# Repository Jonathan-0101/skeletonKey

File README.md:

# Skeleton Key

Final year BEng Project, creating a Penetration Testing Device based on an ESP32 microcontroller, to highlight common and prevelent security vulnerabilities in devices and networks.

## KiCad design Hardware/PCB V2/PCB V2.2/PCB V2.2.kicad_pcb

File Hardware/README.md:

# Project Hardware

The schematics and PCB designs for the device are contained in this directory, designed in KiCad.

It would not have been possible to create the project without the assistance of open source designs and resources, most notibly from [Adafruit Industries](https://github.com/adafruit) and [Flipper Devices](https://github.com/flipperdevices)

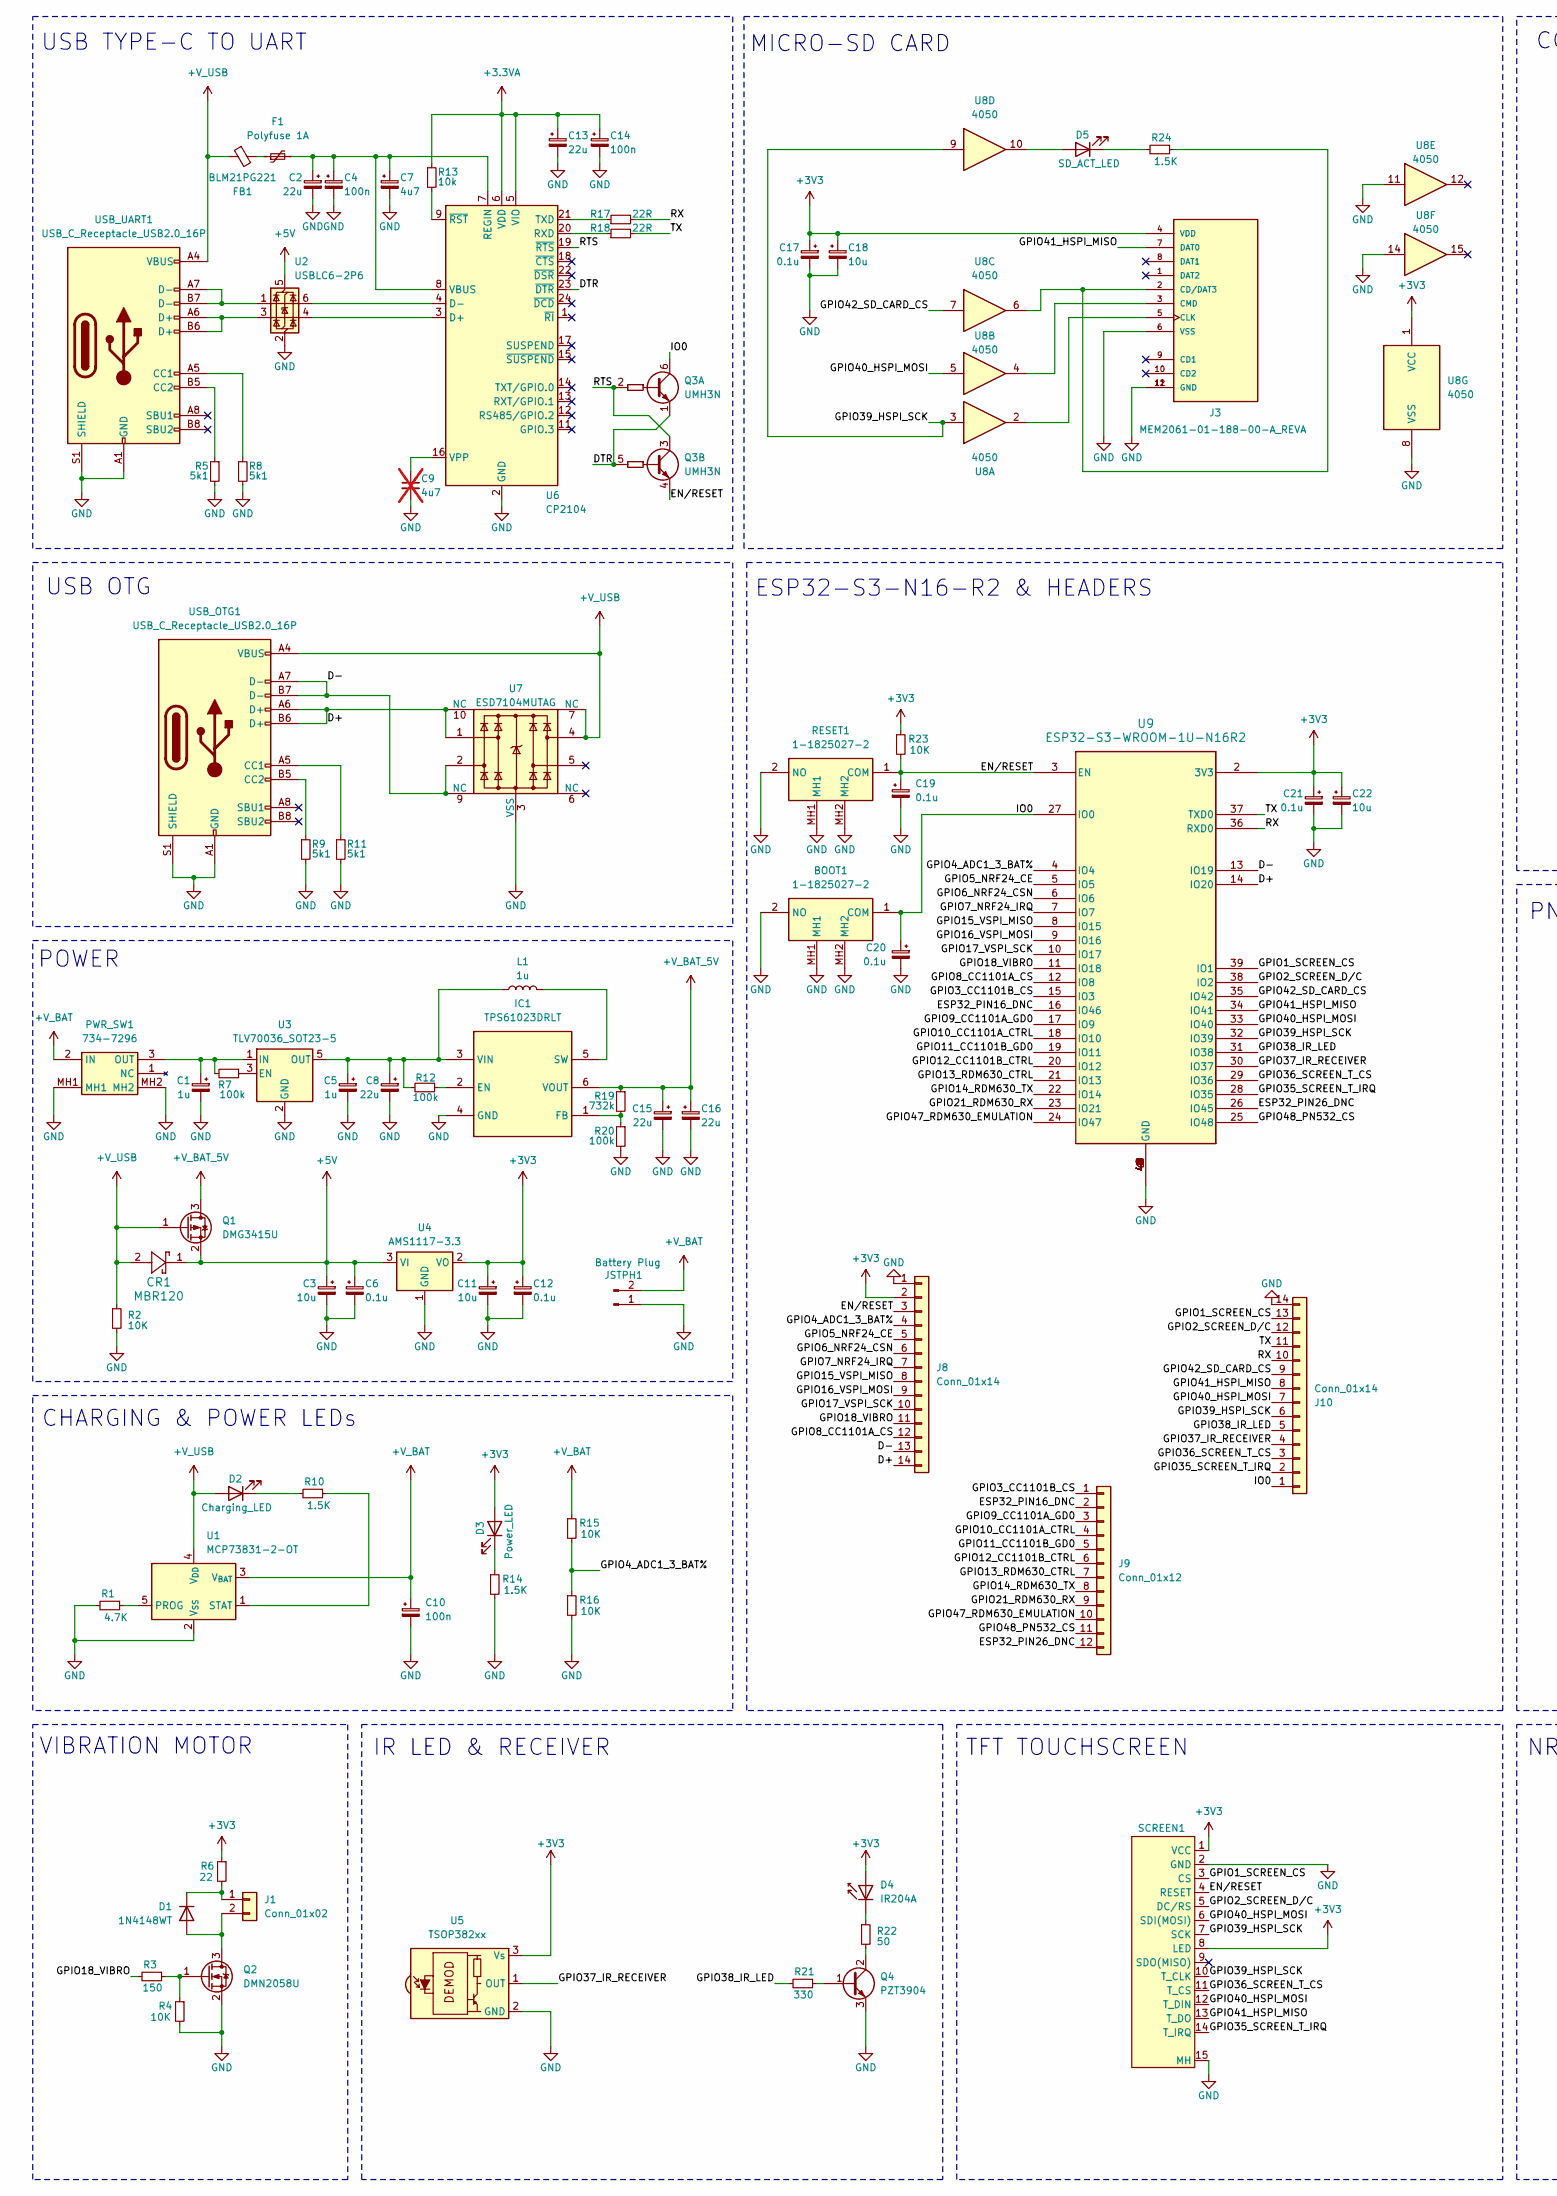
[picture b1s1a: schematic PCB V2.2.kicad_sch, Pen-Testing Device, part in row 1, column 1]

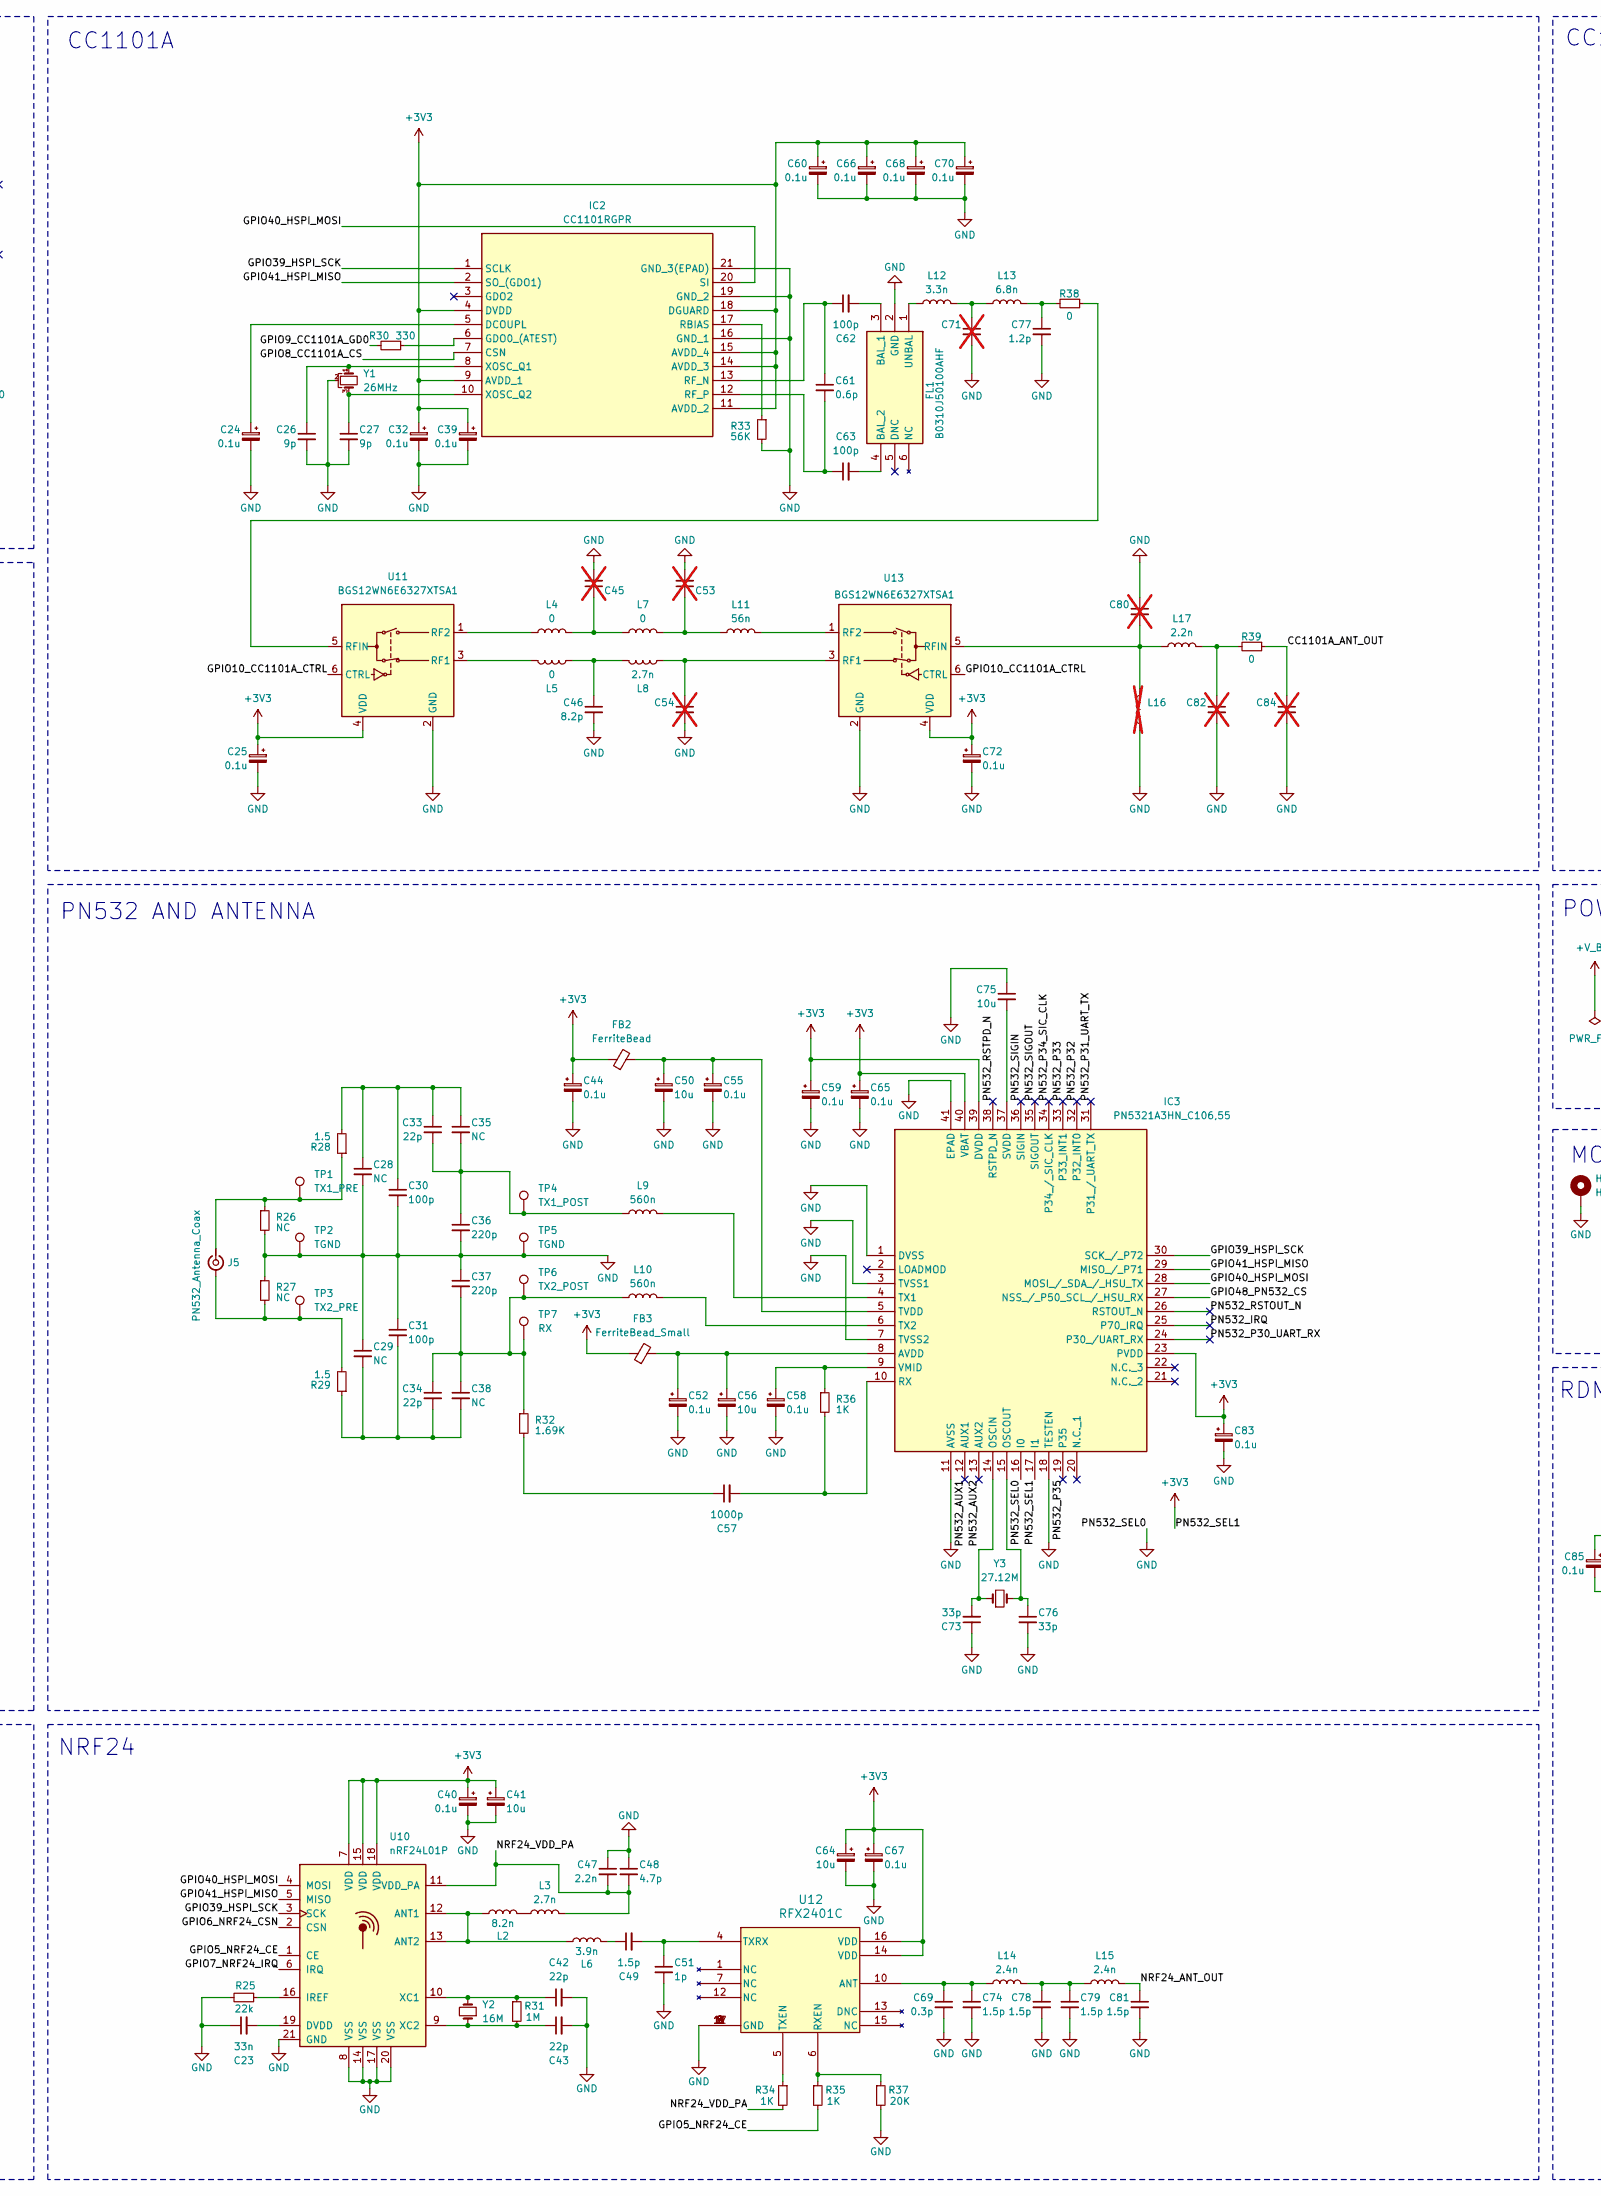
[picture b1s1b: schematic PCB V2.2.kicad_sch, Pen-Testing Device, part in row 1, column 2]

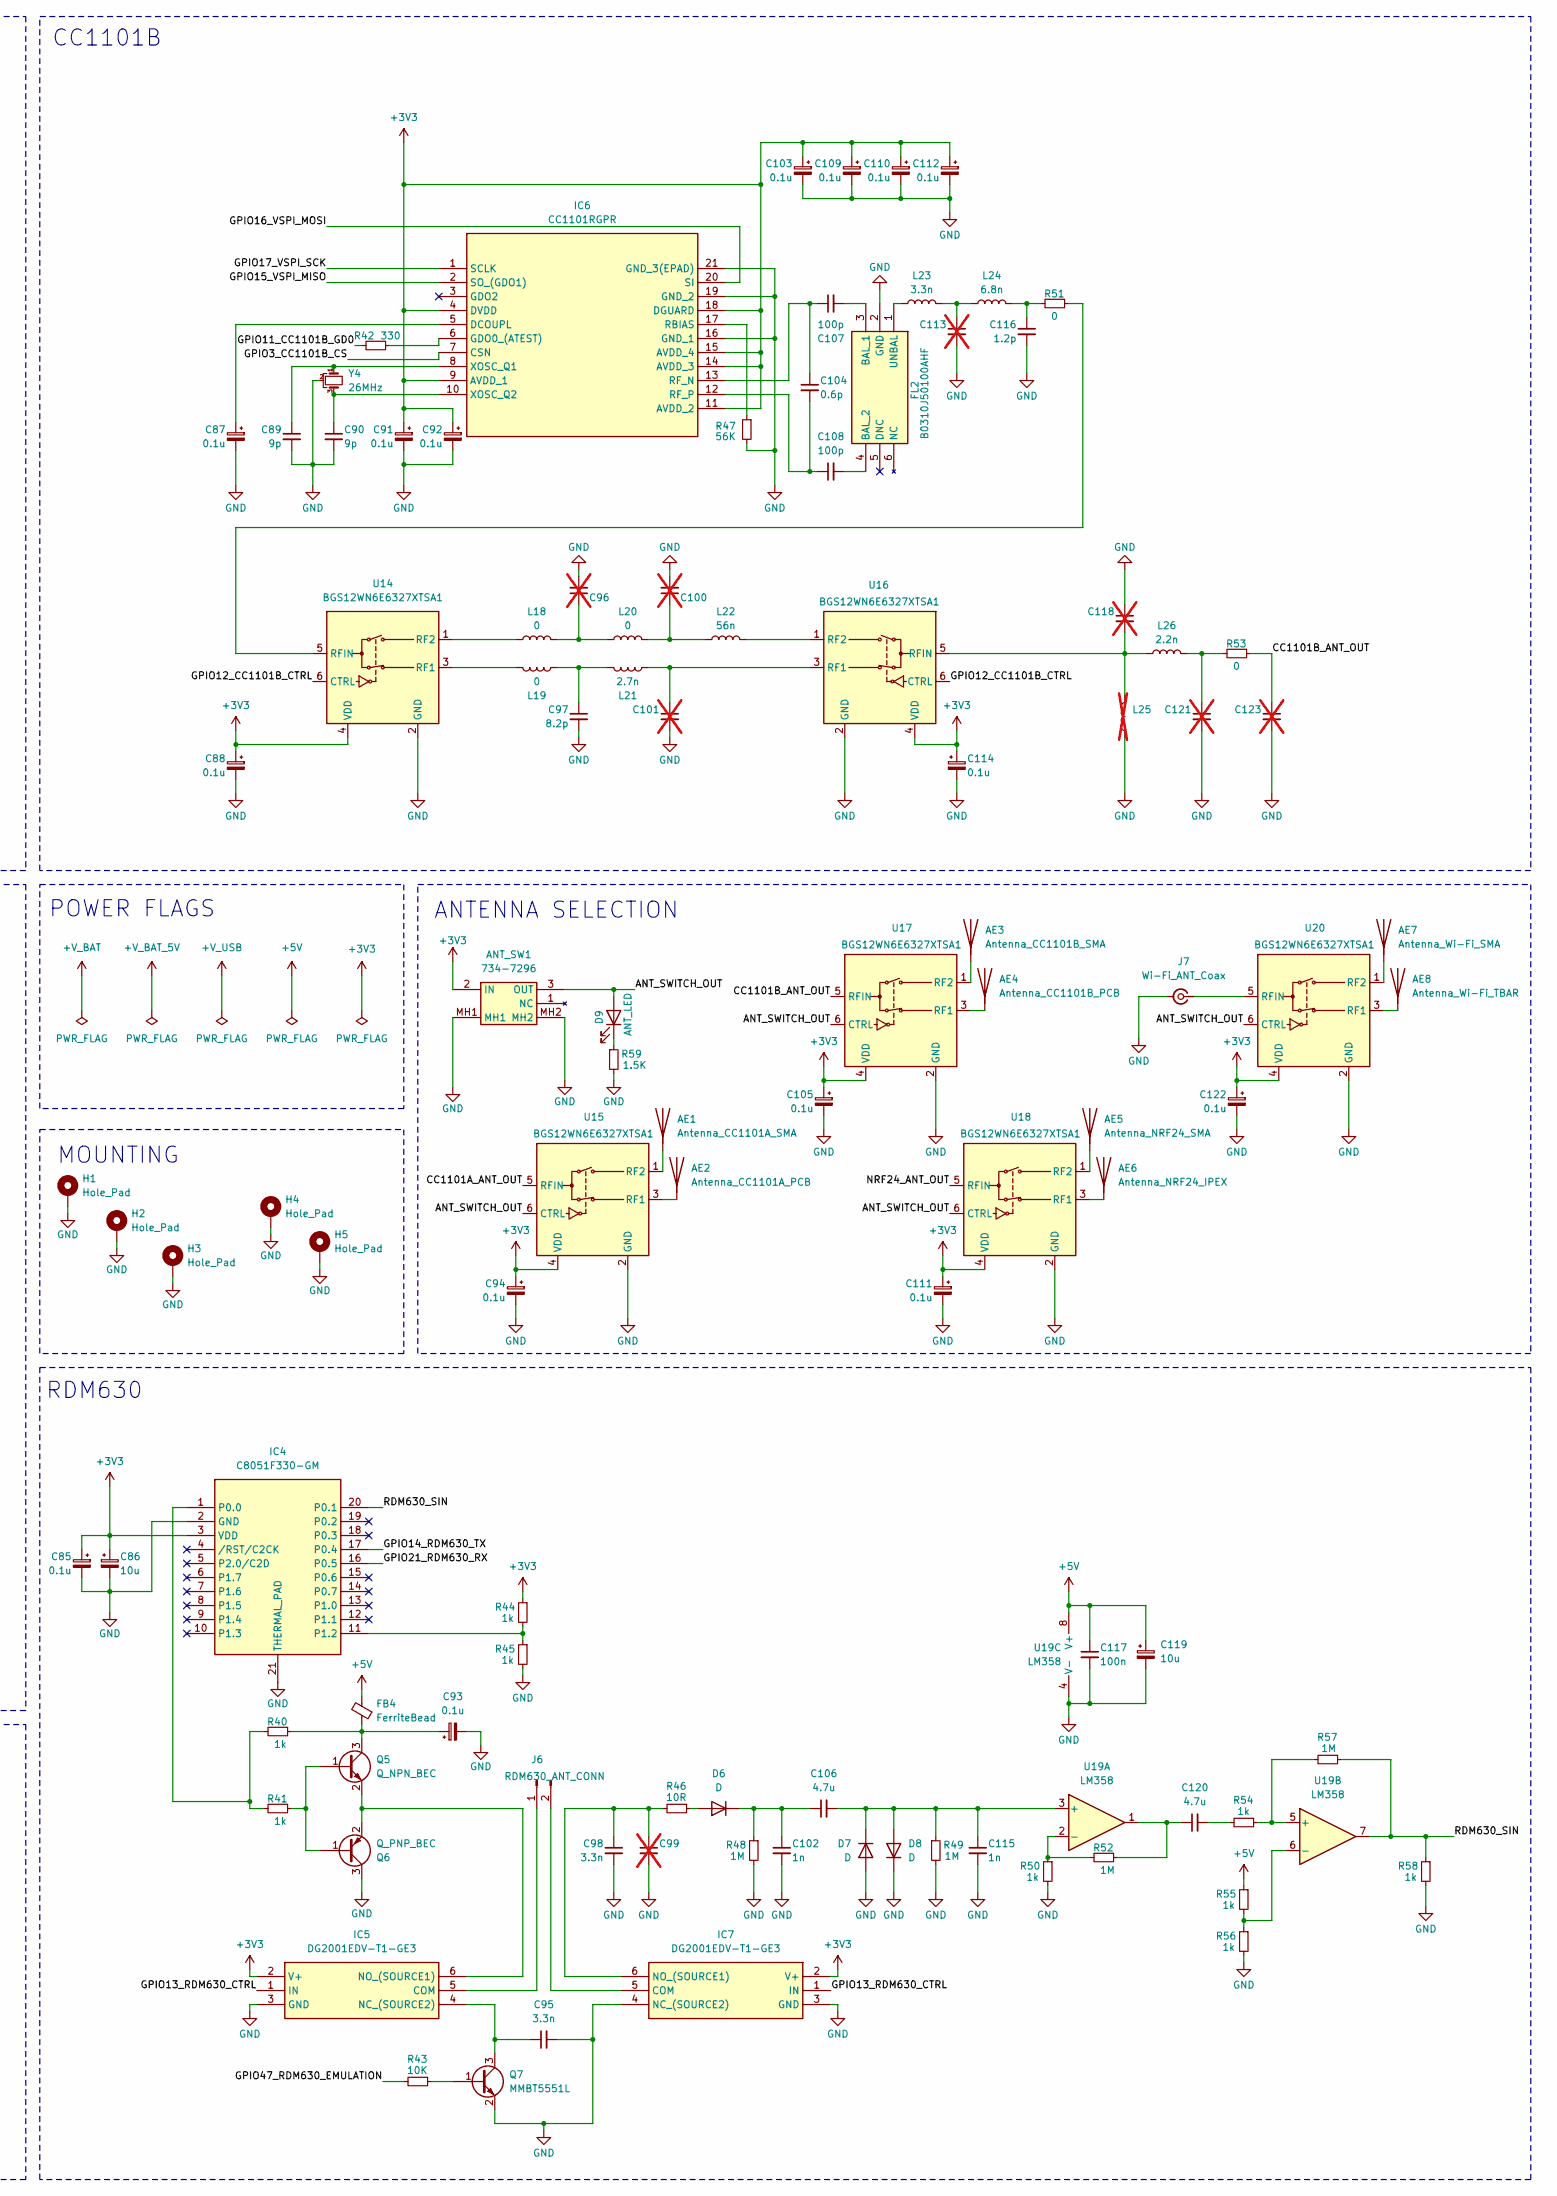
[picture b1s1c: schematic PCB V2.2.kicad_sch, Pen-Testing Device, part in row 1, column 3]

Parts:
AE1: Antenna_CC1101A_SMA; SMA_Molex_73251-1153_EdgeMount_Horizontal
AE2: Antenna_CC1101A_PCB; XDCR_ANT-433-HESM
AE3: Antenna_CC1101B_SMA; SMA_Molex_73251-1153_EdgeMount_Horizontal
AE4: Antenna_CC1101B_PCB; XDCR_ANT-433-HESM
AE5: Antenna_NRF24_SMA; SMA_Molex_73251-1153_EdgeMount_Horizontal
AE6: Antenna_NRF24_IPEX; U.FL_Molex_MCRF_73412-0110_Vertical
AE7: Antenna_Wi-Fi_SMA; SMA_Molex_73251-1153_EdgeMount_Horizontal
AE8: Antenna_Wi-Fi_TBAR; U.FL_Molex_MCRF_73412-0110_Vertical
ANT_SW1: 734-7296; PWR-SW; Manufacturer_Part_Number 734-7296
BOOT1: 1-1825027-2; 118250272; Mouser Part Number 506-1-1825027-2
C1, C5: 1u; CP_EIA-2012-12_Kemet-R_Pad1.30x1.05mm_HandSolder
C2, C8, C13, C15, C16: 22u; CP_EIA-2012-12_Kemet-R_Pad1.30x1.05mm_HandSolder
C3, C11, C18, C22, C41, C56, C64, C86, C119: 10u; CP_EIA-2012-12_Kemet-R_Pad1.30x1.05mm_HandSolder
C4, C10, C14: 100n; CP_EIA-2012-12_Kemet-R_Pad1.30x1.05mm_HandSolder
C6, C12, C17, C19, C20, C21, C24, C25, C32, C39, C40, C52, C58, C60, C66, C67, C68, C70, C72, C85, C87, C88, C91, C92, C93, C94, C103, C105, C109, C110, C111, C112, C114, C122: 0.1u; CP_EIA-2012-12_Kemet-R_Pad1.30x1.05mm_HandSolder
C7: 4u7; CP_EIA-2012-12_Kemet-R_Pad1.30x1.05mm_HandSolder
C9: 4u7; C_0805_2012Metric_Pad1.18x1.45mm_HandSolder; not fitted
C23: 33n; C_0805_2012Metric_Pad1.18x1.45mm_HandSolder
C26, C27, C89, C90: 9p; C_0805_2012Metric_Pad1.18x1.45mm_HandSolder
C28, C29, C35, C38: NC; C_0805_2012Metric_Pad1.18x1.45mm_HandSolder
C30, C31, C62, C63, C107, C108: 100p; C_0805_2012Metric_Pad1.18x1.45mm_HandSolder
C33, C34, C42, C43: 22p; C_0805_2012Metric_Pad1.18x1.45mm_HandSolder
C36, C37: 220p; C_0805_2012Metric_Pad1.18x1.45mm_HandSolder
C44, C55, C59, C65, C83: 0.1u; C_0805_2012Metric_Pad1.18x1.45mm_HandSolder
C45, C53, C54, C71, C80, C82, C84, C96, C99, C100, C101, C113, C118, C121, C123: C_0805_2012Metric_Pad1.18x1.45mm_HandSolder; not fitted
C46, C97: 8.2p; C_0805_2012Metric_Pad1.18x1.45mm_HandSolder
C47: 2.2n; C_0805_2012Metric_Pad1.18x1.45mm_HandSolder
C48: 4.7p; C_0805_2012Metric_Pad1.18x1.45mm_HandSolder
C49, C74, C78, C79, C81: 1.5p; C_0805_2012Metric_Pad1.18x1.45mm_HandSolder
C50, C75: 10u; C_0805_2012Metric_Pad1.18x1.45mm_HandSolder
C51: 1p; C_0805_2012Metric_Pad1.18x1.45mm_HandSolder
C57: 1000p; C_0805_2012Metric_Pad1.18x1.45mm_HandSolder
C61, C104: 0.6p; C_0805_2012Metric_Pad1.18x1.45mm_HandSolder
C69: 0.3p; C_0805_2012Metric_Pad1.18x1.45mm_HandSolder
C73, C76: 33p; C_0805_2012Metric_Pad1.18x1.45mm_HandSolder
C77, C116: 1.2p; C_0805_2012Metric_Pad1.18x1.45mm_HandSolder
C95, C98: 3.3n; C_1206_3216Metric_Pad1.33x1.80mm_HandSolder
C102, C115: 1n; C_0805_2012Metric_Pad1.18x1.45mm_HandSolder
C106, C120: 4.7u; C_0805_2012Metric_Pad1.18x1.45mm_HandSolder
C117: 100n; C_0805_2012Metric_Pad1.18x1.45mm_HandSolder
CR1: MBR120; SDO_SOD-123FL498_OSI
D1: 1N4148WT; D_SOD-523
D2: Charging_LED; LED_0805_2012Metric_Pad1.15x1.40mm_HandSolder
D3: Power_LED; LED_0805_2012Metric_Pad1.15x1.40mm_HandSolder
D4: IR204A; LED_D3.0mm_IRBlack
D5: SD_ACT_LED; LED_0805_2012Metric_Pad1.15x1.40mm_HandSolder
D6, D7, D8: D; D_0805_2012Metric_Pad1.15x1.40mm_HandSolder
D9: ANT_LED; LED_0805_2012Metric_Pad1.15x1.40mm_HandSolder
F1: Polyfuse 1A; Fuse_1206_3216Metric_Pad1.42x1.75mm_HandSolder
FB1: BLM21PG221; L_0603_1608Metric_Pad1.05x0.95mm_HandSolder
FB2, FB4: FerriteBead; BEADC2012X145N
FB3: FerriteBead_Small; BEADC2012X145N
FL1, FL2: B0310J50100AHF; Mouser Part Number 620-B0310J50100AHF
H1, H2, H3, H4, H5: Hole_Pad; MountingHole_2.2mm_M2_Pad_Via
IC1: TPS61023DRLT; SOTFL50P160X60-6N; Mouser Part Number 595-TPS61023DRLT
IC2, IC6: CC1101RGPR; QFN50P400X400X100-21N-D; Mouser Part Number 595-CC1101RGPR
IC3: PN5321A3HN_C106,55; HVQFN-40-1EP_6x6mm_P0.5mm_EP4.1x4.1mm_ThermalVias; Mouser Part Number 771-PN5321A3HNC10
IC4: C8051F330-GM; QFN50P400X400X100-21N-D; Mouser Part Number 634-C8051F330-GM
IC5, IC7: DG2001EDV-T1-GE3; SOT95P284X110-6N; Mouser Part Number 78-DG2001EDV-T1-GE3
J1: Conn_01x02; PinSocket_1x02_P2.54mm_Vertical
J3: MEM2061-01-188-00-A_REVA; GCT_MEM2061-01-188-00-A_REVA
J5: PN532_Antenna_Coax; U.FL_Molex_MCRF_73412-0110_Vertical
J6: RDM630_ANT_CONN; PinHeader_1x02_P2.54mm_Vertical
J7: Wi-Fi_ANT_Coax; U.FL_Molex_MCRF_73412-0110_Vertical
J8, J10: Conn_01x14; PinSocket_1x14_P1.27mm_Vertical
J9: Conn_01x12; PinSocket_1x12_P1.27mm_Vertical
JSTPH1: Battery Plug; JST_PH_S2B-PH-K_1x02_P2.00mm_Horizontal
L1: 1u; L_Changjiang_FNR5045S
L2: 8.2n; L_0805_2012Metric_Pad1.15x1.40mm_HandSolder
L3, L8, L21: 2.7n; L_0805_2012Metric_Pad1.15x1.40mm_HandSolder
L4, L5, L7, L18, L19, L20: 0; L_0805_2012Metric_Pad1.15x1.40mm_HandSolder
L6: 3.9n; L_0805_2012Metric_Pad1.15x1.40mm_HandSolder
L9, L10: 560n; L_0805_2012Metric_Pad1.15x1.40mm_HandSolder
L11, L22: 56n; L_0805_2012Metric_Pad1.15x1.40mm_HandSolder
L12, L23: 3.3n; L_0805_2012Metric_Pad1.15x1.40mm_HandSolder
L13, L24: 6.8n; L_0805_2012Metric_Pad1.15x1.40mm_HandSolder
L14, L15: 2.4n; L_0805_2012Metric_Pad1.15x1.40mm_HandSolder
L16, L25: L_0805_2012Metric_Pad1.15x1.40mm_HandSolder; not fitted
L17, L26: 2.2n; L_0805_2012Metric_Pad1.15x1.40mm_HandSolder
PWR_SW1: 734-7296; PWR-SW; Manufacturer_Part_Number 734-7296
Q1: DMG3415U; SOT95P240X105-3N
Q2: DMN2058U; SOT-23
Q3: UMH3N; SOT-363_SC-70-6
Q4: PZT3904; SOT-223-3_TabPin2
Q5: Q_NPN_BEC; TSOT-23_HandSoldering
Q6: Q_PNP_BEC; TSOT-23_HandSoldering
Q7: MMBT5551L; SOT-23
R1: 4.7K; R_0805_2012Metric_Pad1.20x1.40mm_HandSolder
R2, R4, R15, R16, R23, R43: 10K; R_0805_2012Metric_Pad1.20x1.40mm_HandSolder
R3: 150; R_0805_2012Metric_Pad1.20x1.40mm_HandSolder
R5, R8, R9, R11: 5k1; R_0805_2012Metric_Pad1.20x1.40mm_HandSolder
R6: 22; R_0805_2012Metric_Pad1.20x1.40mm_HandSolder
R7, R12, R20: 100k; R_0805_2012Metric_Pad1.20x1.40mm_HandSolder
R10, R14, R24, R59: 1.5K; R_0805_2012Metric_Pad1.20x1.40mm_HandSolder
R13: 10k; R_0805_2012Metric_Pad1.20x1.40mm_HandSolder
R17, R18: 22R; R_0805_2012Metric_Pad1.20x1.40mm_HandSolder
R19: 732k; R_0805_2012Metric_Pad1.20x1.40mm_HandSolder
R21, R30, R42: 330; R_0805_2012Metric_Pad1.20x1.40mm_HandSolder
R22: 50; R_0805_2012Metric_Pad1.20x1.40mm_HandSolder
R25: 22k; R_0805_2012Metric_Pad1.20x1.40mm_HandSolder
R26, R27: NC; R_0805_2012Metric_Pad1.20x1.40mm_HandSolder
R28, R29: 1.5; R_0805_2012Metric_Pad1.20x1.40mm_HandSolder
R31, R48, R49, R52, R57: 1M; R_0805_2012Metric_Pad1.20x1.40mm_HandSolder
R32: 1.69K; R_0805_2012Metric_Pad1.20x1.40mm_HandSolder
R33, R47: 56K; R_0805_2012Metric_Pad1.20x1.40mm_HandSolder
R34, R35, R36: 1K; R_0805_2012Metric_Pad1.20x1.40mm_HandSolder
R37: 20K; R_0805_2012Metric_Pad1.20x1.40mm_HandSolder
R38, R39, R51, R53: 0; R_0805_2012Metric_Pad1.20x1.40mm_HandSolder
R40, R41, R44, R45, R50, R54, R55, R56, R58: 1k; R_0805_2012Metric_Pad1.20x1.40mm_HandSolder
R46: 10R; R_0805_2012Metric_Pad1.20x1.40mm_HandSolder
RESET1: 1-1825027-2; 118250272; Mouser Part Number 506-1-1825027-2
SCREEN1: 4.0_TFT_Display
TP1: TX1_PRE; TestPoint_Pad_D1.0mm
TP2, TP5: TGND; TestPoint_Pad_D1.0mm
TP3: TX2_PRE; TestPoint_Pad_D1.0mm
TP4: TX1_POST; TestPoint_Pad_D1.0mm
TP6: TX2_POST; TestPoint_Pad_D1.0mm
TP7: RX; TestPoint_Pad_D1.0mm
U1: MCP73831-2-OT; SOT-23-5
U2: USBLC6-2P6; SOT-666
U3: TLV70036_SOT23-5; SOT-23-5
U4: AMS1117-3.3; SOT-223-3_TabPin2
U5: TSOP382xx; Vishay_MINICAST-3Pin
U6: CP2104; QFN-24-1EP_4x4mm_P0.5mm_EP2.6x2.6mm
U7: ESD7104MUTAG; Diodes_UDFN-10_1.0x2.5mm_P0.5mm
U8: 4050; SOIC-16_3.9x9.9mm_P1.27mm
U9: ESP32-S3-WROOM-1U-N16R2; ESP32-S3-WROOM-1U_EXP
U10: nRF24L01P; QFN-20-1EP_4x4mm_P0.5mm_EP2.5x2.5mm
U11, U13, U14, U15, U16, U17, U18, U20: BGS12WN6E6327XTSA1; Infineon_PG-TSNP-6-10_0.7x1.1mm_0.7x1.1mm_P0.4mm
U12: RFX2401C; RFX2401C_SKY
U19: LM358; SOIC127P600X175-8N
USB_OTG1: USB_C_Receptacle_USB2.0_16P; USB_C_Receptacle_HRO_TYPE-C-31-M-12
USB_UART1: USB_C_Receptacle_USB2.0_16P; USB_C_Receptacle_HRO_TYPE-C-31-M-12
Y1, Y4: 26MHz; Crystal_SMD_3225-4Pin_3.2x2.5mm_HandSoldering
Y2: 16M; XTAL_7M-27.120MAAJ-T
Y3: 27.12M; XTAL_7M-27.120MAAJ-T

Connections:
+3.3VA: C13.1, C14.1, R13.1, U6.5 (VIO), U6.6 (VDD)
+3V3: ANT_SW1.2 (IN), C11.1, C12.1, C17.1, C18.1, C21.1, C22.1, C25.1, C32.1, C39.1, C40.1, C41.1, C44.1, C59.1, C60.1, C64.1, C65.1, C66.1, C67.1, C68.1, C70.1, C72.1, C83.1, C85.1, C86.1, C88.1, C91.1, C92.1, C94.1, C103.1, C105.1, C109.1, C110.1, C111.1, C112.1, C114.1, C122.1, D3.2 (A), D4.2 (A), FB2.1, FB3.1, IC2.4 (DVDD), IC2.9 (AVDD_1), IC2.11 (AVDD_2), IC2.14 (AVDD_3), IC2.15 (AVDD_4), IC2.18 (DGUARD), IC3.17 (I1), IC3.23 (PVDD), IC3.39 (DVDD), IC3.40 (VBAT), IC4.3 (VDD), IC5.2 (V+), IC6.4 (DVDD), IC6.9 (AVDD_1), IC6.11 (AVDD_2), IC6.14 (AVDD_3), IC6.15 (AVDD_4), IC6.18 (DGUARD), IC7.2 (V+), J3.4 (VDD), J8.2, R6.1, R23.1, R44.1, SCREEN1.1 (VCC), SCREEN1.8 (LED), U4.2 (VO), U5.3 (Vs), U8.1 (VCC), U9.2 (3V3), U10.7 (VDD), U10.15 (VDD), U10.18 (VDD), U11.4 (VDD), U12.14 (VDD), U12.16 (VDD), U13.4 (VDD), U14.4 (VDD), U15.4 (VDD), U16.4 (VDD), U17.4 (VDD), U18.4 (VDD), U20.4 (VDD)
+5V: C3.1, C6.1, C117.1, C119.1, CR1.1, FB4.2, Q1.2 (S), R55.1, U2.5 (VBUS), U4.3 (VI), U19.8 (V+)
+V_BAT: C10.1, JSTPH1.2, PWR_SW1.2 (IN), R15.1, U1.3 (V_{BAT})
+V_BAT_5V: C15.1, C16.1, IC1.6 (VOUT), Q1.3 (D), R19.1
+V_USB: CR1.2, D2.2 (A), FB1.1, Q1.1 (G), R2.1, U1.4 (V_{DD}), U7.4, U7.7 (NC), USB_OTG1.A4 (VBUS), USB_OTG1.A9 (VBUS), USB_OTG1.B4 (VBUS), USB_OTG1.B9 (VBUS), USB_UART1.A4 (VBUS), USB_UART1.A9 (VBUS), USB_UART1.B4 (VBUS), USB_UART1.B9 (VBUS)
/ANT_SWITCH_OUT: ANT_SW1.3 (OUT), D9.2 (A), U15.6 (CTRL), U17.6 (CTRL), U18.6 (CTRL), U20.6 (CTRL)
/CC1101A_ANT_OUT: C84.1, R39.1, U15.5 (RFIN)
/CC1101B_ANT_OUT: C123.1, R53.1, U17.5 (RFIN)
/D+: J8.14, U7.1, U7.10 (NC), U9.14 (IO20), USB_OTG1.A6 (D+), USB_OTG1.B6 (D+)
/D-: J8.13, U7.2, U7.9 (NC), U9.13 (IO19), USB_OTG1.A7 (D-), USB_OTG1.B7 (D-)
/DTR: Q3.1 (E1), Q3.5 (B2), U6.23 (~DTR)
/EN/RESET: C19.1, J8.3, Q3.4 (E2), R23.2, RESET1.1 (COM), SCREEN1.4 (RESET), U9.3 (EN)
/ESP32_PIN16_DNC: J9.2, U9.16 (IO46)
/ESP32_PIN26_DNC: J9.12, U9.26 (IO45)
/GPIO1_SCREEN_CS: J10.13, SCREEN1.3 (CS), U9.39 (IO1)
/GPIO2_SCREEN_D/C: J10.12, SCREEN1.5 (DC/RS), U9.38 (IO2)
/GPIO3_CC1101B_CS: IC6.7 (CSN), J9.1, U9.15 (IO3)
/GPIO4_ADC1_3_BAT%: J8.4, R15.2, R16.1, U9.4 (IO4)
/GPIO5_NRF24_CE: J8.5, R35.2, U9.5 (IO5), U10.1 (CE)
/GPIO6_NRF24_CSN: J8.6, U9.6 (IO6), U10.2 (CSN)
/GPIO7_NRF24_IRQ: J8.7, U9.7 (IO7), U10.6 (IRQ)
/GPIO8_CC1101A_CS: IC2.7 (CSN), J8.12, U9.12 (IO8)
/GPIO9_CC1101A_GD0: J9.3, R30.2, U9.17 (IO9)
/GPIO10_CC1101A_CTRL: J9.4, U9.18 (IO10), U11.6 (CTRL), U13.6 (CTRL)
/GPIO11_CC1101B_GD0: J9.5, R42.2, U9.19 (IO11)
/GPIO12_CC1101B_CTRL: J9.6, U9.20 (IO12), U14.6 (CTRL), U16.6 (CTRL)
/GPIO13_RDM630_CTRL: IC5.1 (IN), IC7.1 (IN), J9.7, U9.21 (IO13)
/GPIO14_RDM630_TX: IC4.17 (P0.4), J9.8, U9.22 (IO14)
/GPIO15_VSPI_MISO: IC6.2 (SO_(GDO1)), J8.8, U9.8 (IO15)
/GPIO16_VSPI_MOSI: IC6.20 (SI), J8.9, U9.9 (IO16)
/GPIO17_VSPI_SCK: IC6.1 (SCLK), J8.10, U9.10 (IO17)
/GPIO18_VIBRO: J8.11, R3.2, U9.11 (IO18)
/GPIO21_RDM630_RX: IC4.16 (P0.5), J9.9, U9.23 (IO21)
/GPIO35_SCREEN_T_IRQ: J10.2, SCREEN1.14 (T_IRQ), U9.28 (IO35)
/GPIO36_SCREEN_T_CS: J10.3, SCREEN1.11 (T_CS), U9.29 (IO36)
/GPIO37_IR_RECEIVER: J10.4, U5.1 (OUT), U9.30 (IO37)
/GPIO38_IR_LED: J10.5, R21.2, U9.31 (IO38)
/GPIO39_HSPI_SCK: IC2.1 (SCLK), IC3.30 (SCK_/_P72), J10.6, SCREEN1.7 (SCK), SCREEN1.10 (T_CLK), U8.3, U8.9, U9.32 (IO39), U10.3 (SCK)
/GPIO40_HSPI_MOSI: IC2.20 (SI), IC3.28 (MOSI_/_SDA_/_HSU_TX), J10.7, SCREEN1.6 (SDI(MOSI)), SCREEN1.12 (T_DIN), U8.5, U9.33 (IO40), U10.4 (MOSI)
/GPIO41_HSPI_MISO: IC2.2 (SO_(GDO1)), IC3.29 (MISO_/_P71), J3.7 (DAT0), J10.8, SCREEN1.13 (T_DO), U9.34 (IO41), U10.5 (MISO)
/GPIO42_SD_CARD_CS: J10.9, U8.7, U9.35 (IO42)
/GPIO47_RDM630_EMULATION: J9.10, R43.2, U9.24 (IO47)
/GPIO48_PN532_CS: IC3.27 (NSS_/_P50_SCL_/_HSU_RX), J9.11, U9.25 (IO48)
/IO0: BOOT1.1 (COM), C20.1, J10.1, Q3.6 (C1), U9.27 (IO0)
/NRF24_ANT_OUT: C81.1, L15.2, U18.5 (RFIN)
/NRF24_VDD_PA: C47.2, C48.2, L3.2, R34.2, U10.11 (VDD_PA)
/PN532_AUX1: IC3.12 (AUX1)
/PN532_AUX2: IC3.13 (AUX2)
/PN532_IRQ: IC3.25 (P70_IRQ)
/PN532_P30_UART_RX: IC3.24 (P30_/UART_RX)
/PN532_P31_UART_TX: IC3.31 (P31_/_UART_TX)
/PN532_P32: IC3.32 (P32_INT0)
/PN532_P33: IC3.33 (P33_INT1)
/PN532_P34_SIC_CLK: IC3.34 (P34_/_SIC_CLK)
/PN532_P35: IC3.19 (P35)
/PN532_RSTOUT_N: IC3.26 (RSTOUT_N)
/PN532_RSTPD_N: IC3.38 (RSTPD_N)
/PN532_SIGIN: IC3.36 (SIGIN)
/PN532_SIGOUT: IC3.35 (SIGOUT)
/RDM630_SIN: IC4.20 (P0.1), R57.1, R58.1, U19.7
/RTS: Q3.2 (B1), Q3.3 (C2), U6.19 (~RTS)
/RX: J10.10, R17.2, U9.36 (RXD0)
/TX: J10.11, R18.2, U9.37 (TXD0)
GND: ANT_SW1.MH1, ANT_SW1.MH2, BOOT1.2 (NO), BOOT1.MH1, BOOT1.MH2, C1.2, C2.2, C3.2, C4.2, C5.2, C6.2, C7.2, C8.2, C9.2, C10.2, C11.2, C12.2, C13.2, C14.2, C15.2, C16.2, C17.2, C18.2, C19.2, C20.2, C21.2, C22.2, C23.1, C24.2, C25.2, C26.2, C27.2, C28.2, C29.1, C30.2, C31.1, C32.2, C36.2, C37.1, C39.2, C40.2, C41.2, C42.2, C43.2, C44.2, C45.2, C46.2, C47.1, C48.1, C50.2, C51.2, C52.2, C53.2, C54.2, C55.2, C56.2, C58.2, C59.2, C60.2, C64.2, C65.2, C66.2, C67.2, C68.2, C69.2, C70.2, C71.2, C72.2, C73.1, C74.2, C75.1, C76.2, C77.2, C78.2, C79.2, C80.1, C81.2, C82.2, C83.2, C84.2, C85.2, C86.2, C87.2, C88.2, C89.2, C90.2, C91.2, C92.2, C93.2, C94.2, C95.2, C96.2, C97.2, C98.2, C99.2, C100.2, C101.2, C102.2, C103.2, C105.2, C109.2, C110.2, C111.2, C112.2, C113.2, C114.2, C115.2, C116.2, C117.2, C118.1, C119.2, C121.2, C122.2, C123.2, D7.2 (A), D8.1 (K), FL1.2 (GND), FL2.2 (GND), H1.1, H2.1, H3.1, H4.1, H5.1, IC1.4 (GND), IC2.16 (GND_1), IC2.19 (GND_2), IC2.21 (GND_3(EPAD)), IC3.1 (DVSS), IC3.3 (TVSS1), IC3.7 (TVSS2), IC3.11 (AVSS), IC3.16 (I0), IC3.18 (TESTEN), IC3.41 (EPAD), IC4.2 (GND), IC4.21 (THERMAL_PAD), IC5.3 (GND), IC6.16 (GND_1), IC6.19 (GND_2), IC6.21 (GND_3(EPAD)), IC7.3 (GND), IC7.4 (NC_(SOURCE2)), J3.6 (VSS), J3.11 (GND), J3.12 (GND), J7.2 (Ext), J8.1, J10.14, JSTPH1.1, L16.1, L25.1, PWR_SW1.MH1, PWR_SW1.MH2, Q2.2 (S), Q4.3 (E), Q6.3 (C), Q7.2 (E), R1.2, R2.2, R4.2, R5.2, R8.2, R9.2, R11.2, R14.2, R16.2, R20.2, R25.2, R26.2, R27.1, R33.2, R37.2, R45.2, R47.2, R48.2, R49.2, R50.2, R56.2, R58.2, R59.2, RESET1.2 (NO), RESET1.MH1, RESET1.MH2, SCREEN1.2 (GND), SCREEN1.15 (MH), TP2.1, TP5.1, U1.2 (V_{SS}), U2.2 (GND), U3.2 (GND), U4.1 (GND), U5.2 (GND), U6.2 (GND), U6.25 (GND), U7.3 (VSS), U7.8 (VSS), U8.8 (VSS), U8.11, U8.14, U9.1 (GND), U9.40 (GND), U9.41 (GND), U9.42 (GND), U9.43 (GND), U9.44 (GND), U9.45 (GND), U9.46 (GND), U9.47 (GND), U9.48 (GND), U9.49 (GND), U10.8 (VSS), U10.14 (VSS), U10.17 (VSS), U10.20 (VSS), U10.21 (GND), U11.2 (GND), U12.2 (GND), U12.3 (GND), U12.8 (GND), U12.9 (GND), U12.11 (GND), U12.17 (GND), U13.2 (GND), U14.2 (GND), U15.2 (GND), U16.2 (GND), U17.2 (GND), U18.2 (GND), U19.4 (V-), U20.2 (GND), USB_OTG1.A1 (GND), USB_OTG1.A12 (GND), USB_OTG1.B1 (GND), USB_OTG1.B12 (GND), USB_OTG1.S1 (SHIELD), USB_UART1.A1 (GND), USB_UART1.A12 (GND), USB_UART1.B1 (GND), USB_UART1.B12 (GND), USB_UART1.S1 (SHIELD), Y1.2, Y4.2
unnamed: AE1.1 (A), U15.1 (RF2)
unnamed: AE2.1 (A), U15.3 (RF1)
unnamed: AE3.1 (A), U17.1 (RF2)
unnamed: AE4.1 (A), U17.3 (RF1)
unnamed: AE5.1 (A), U18.1 (RF2)
unnamed: AE6.1 (A), U18.3 (RF1)
unnamed: AE7.1 (A), U20.1 (RF2)
unnamed: AE8.1 (A), U20.3 (RF1)
unnamed: C28.1, C30.1, C33.1, C35.1, R28.2
unnamed: C29.2, C31.2, C34.2, C38.2, R29.1
unnamed: C33.2, C35.2, C36.1, L9.1, TP4.1
unnamed: C34.1, C37.2, C38.1, L10.1, R32.1, TP6.1, TP7.1
unnamed: C45.1, L4.2, L7.1
unnamed: C46.1, L5.2, L8.1
unnamed: C49.1, L6.1
unnamed: C53.1, L7.2, L11.1
unnamed: C57.1, R32.2
unnamed: C71.1, L12.2, L13.1
unnamed: C77.1, L13.2, R38.2
unnamed: C78.1, C79.1, L14.2, L15.1
unnamed: C82.1, L17.2, R39.2
unnamed: C96.1, L18.2, L20.1
unnamed: C97.1, L19.2, L21.1
unnamed: C100.1, L20.2, L22.1
unnamed: C113.1, L23.2, L24.1
unnamed: C116.1, L24.2, R51.2
unnamed: C120.1, R52.1, U19.1
unnamed: C120.2, R54.2
unnamed: C121.1, L26.2, R53.2
unnamed: D1.2 (A), J1.2, Q2.3 (D)
unnamed: D1.1 (K), J1.1, R6.2
unnamed: D2.1 (K), R10.2
unnamed: D3.1 (K), R14.1
unnamed: D4.1 (K), R22.1
unnamed: D5.2 (A), U8.10
unnamed: D5.1 (K), R24.2
unnamed: D6.2 (A), R46.1
unnamed: C102.1, C106.1, D6.1 (K), R48.1
unnamed: C106.2, C115.1, D7.1 (K), D8.2 (A), R49.1, U19.3 (+)
unnamed: D9.1 (K), R59.1
unnamed: F1.1, FB1.2
unnamed: C62.2, FL1.3 (BAL_1)
unnamed: C63.2, FL1.4 (BAL_2)
unnamed: FL1.1 (UNBAL), L12.1
unnamed: C107.2, FL2.3 (BAL_1)
unnamed: C108.2, FL2.4 (BAL_2)
unnamed: FL2.1 (UNBAL), L23.1
unnamed: IC1.2 (EN), R12.1
unnamed: IC1.1 (FB), R19.2, R20.1
unnamed: IC1.5 (SW), L1.2
unnamed: C5.1, C8.1, IC1.3 (VIN), L1.1, R12.2, U3.5 (OUT)
unnamed: C24.1, IC2.5 (DCOUPL)
unnamed: IC2.6 (GDO0_(ATEST)), R30.1
unnamed: IC2.17 (RBIAS), R33.1
unnamed: C61.1, C62.1, IC2.13 (RF_N)
unnamed: C61.2, C63.1, IC2.12 (RF_P)
unnamed: C26.1, IC2.8 (XOSC_Q1), Y1.1
unnamed: C27.1, IC2.10 (XOSC_Q2), Y1.3
unnamed: C52.1, C56.1, FB3.2, IC3.8 (AVDD)
unnamed: C73.2, IC3.14 (OSCIN), Y3.1
unnamed: C76.1, IC3.15 (OSCOUT), Y3.2
unnamed: C57.2, IC3.10 (RX), R36.2
unnamed: C75.2, IC3.37 (SVDD)
unnamed: C50.1, C55.1, FB2.2, IC3.5 (TVDD)
unnamed: IC3.4 (TX1), L9.2
unnamed: IC3.6 (TX2), L10.2
unnamed: C58.1, IC3.9 (VMID), R36.1
unnamed: IC4.1 (P0.0), R40.2, R41.2
unnamed: IC4.11 (P1.2), R44.2, R45.1
unnamed: IC5.5 (COM), J6.1
unnamed: C95.1, IC5.4 (NC_(SOURCE2)), Q7.3 (C)
unnamed: IC5.6 (NO_(SOURCE1)), Q5.2 (E), Q6.2 (E)
unnamed: C87.1, IC6.5 (DCOUPL)
unnamed: IC6.6 (GDO0_(ATEST)), R42.1
unnamed: IC6.17 (RBIAS), R47.1
unnamed: C104.1, C107.1, IC6.13 (RF_N)
unnamed: C104.2, C108.1, IC6.12 (RF_P)
unnamed: C89.1, IC6.8 (XOSC_Q1), Y4.1
unnamed: C90.1, IC6.10 (XOSC_Q2), Y4.3
unnamed: IC7.5 (COM), J6.2
unnamed: C98.1, C99.1, IC7.6 (NO_(SOURCE1)), R46.2
unnamed: J3.2 (CD/DAT3), R24.1, U8.6
unnamed: J3.5 (CLK), U8.2
unnamed: J3.3 (CMD), U8.4
unnamed: J5.2 (Ext), R27.2, R29.2, TP3.1
unnamed: J5.1 (In), R26.1, R28.1, TP1.1
unnamed: J7.1 (In), U20.5 (RFIN)
unnamed: L2.1, L3.1
unnamed: C1.1, PWR_SW1.3 (OUT), R7.2, U3.1 (IN)
unnamed: Q2.1 (G), R3.1, R4.1
unnamed: Q4.1 (B), R21.1
unnamed: Q4.2 (C), Q4.4 (C), R22.2
unnamed: Q5.1 (B), Q6.1 (B), R41.1
unnamed: C93.1, FB4.1, Q5.3 (C), R40.1
unnamed: Q7.1 (B), R43.1
unnamed: R1.1, U1.5 (PROG)
unnamed: R10.1, U1.1 (STAT)
unnamed: U2.1 (I/O1), USB_UART1.A7 (D-), USB_UART1.B7 (D-)
unnamed: U2.3 (I/O2), USB_UART1.A6 (D+), USB_UART1.B6 (D+)
unnamed: R7.1, U3.3 (EN)
unnamed: U2.4 (I/O2), U6.3 (D+)
unnamed: U2.6 (I/O1), U6.4 (D-)
unnamed: C2.1, C4.1, C7.1, F1.2, U6.7 (REGIN), U6.8 (VBUS)
unnamed: R18.1, U6.20 (RXD)
unnamed: R17.1, U6.21 (TXD)
unnamed: C9.1, U6.16 (VPP)
unnamed: R13.2, U6.9 (~RST)
unnamed: L2.2, L6.2, U10.12 (ANT1), U10.13 (ANT2)
unnamed: C23.2, U10.19 (DVDD)
unnamed: R25.1, U10.16 (IREF)
unnamed: C42.1, R31.1, U10.10 (XC1), Y2.2
unnamed: C43.1, R31.2, U10.9 (XC2), Y2.1
unnamed: L5.1, U11.3 (RF1)
unnamed: L4.1, U11.1 (RF2)
unnamed: R38.1, U11.5 (RFIN)
unnamed: C69.1, C74.1, L14.1, U12.10 (ANT)
unnamed: R35.1, R37.1, U12.6 (RXEN)
unnamed: R34.1, U12.5 (TXEN)
unnamed: C49.2, C51.1, U12.4 (TXRX)
unnamed: C54.1, L8.2, U13.3 (RF1)
unnamed: L11.2, U13.1 (RF2)
unnamed: C80.2, L16.2, L17.1, U13.5 (RFIN)
unnamed: L19.1, U14.3 (RF1)
unnamed: L18.1, U14.1 (RF2)
unnamed: R51.1, U14.5 (RFIN)
unnamed: C101.1, L21.2, U16.3 (RF1)
unnamed: L22.2, U16.1 (RF2)
unnamed: C118.2, L25.2, L26.1, U16.5 (RFIN)
unnamed: R50.1, R52.2, U19.2 (-)
unnamed: R54.1, R57.2, U19.5 (+)
unnamed: R55.2, R56.1, U19.6 (-)
unnamed: R11.1, USB_OTG1.A5 (CC1)
unnamed: R9.1, USB_OTG1.B5 (CC2)
unnamed: R8.1, USB_UART1.A5 (CC1)
unnamed: R5.1, USB_UART1.B5 (CC2)

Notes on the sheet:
ESP32-S3-N16-R2 & HEADERS
PN532 AND ANTENNA
VIBRATION MOTOR
MOUNTING
NRF24
MICRO-SD CARD
ANTENNA SELECTION
RDM630
POWER FLAGS
TFT TOUCHSCREEN
USB TYPE-C TO UART
IR LED & RECEIVER
CC1101A
POWER
CC1101B
CHARGING & POWER LEDs
USB OTG

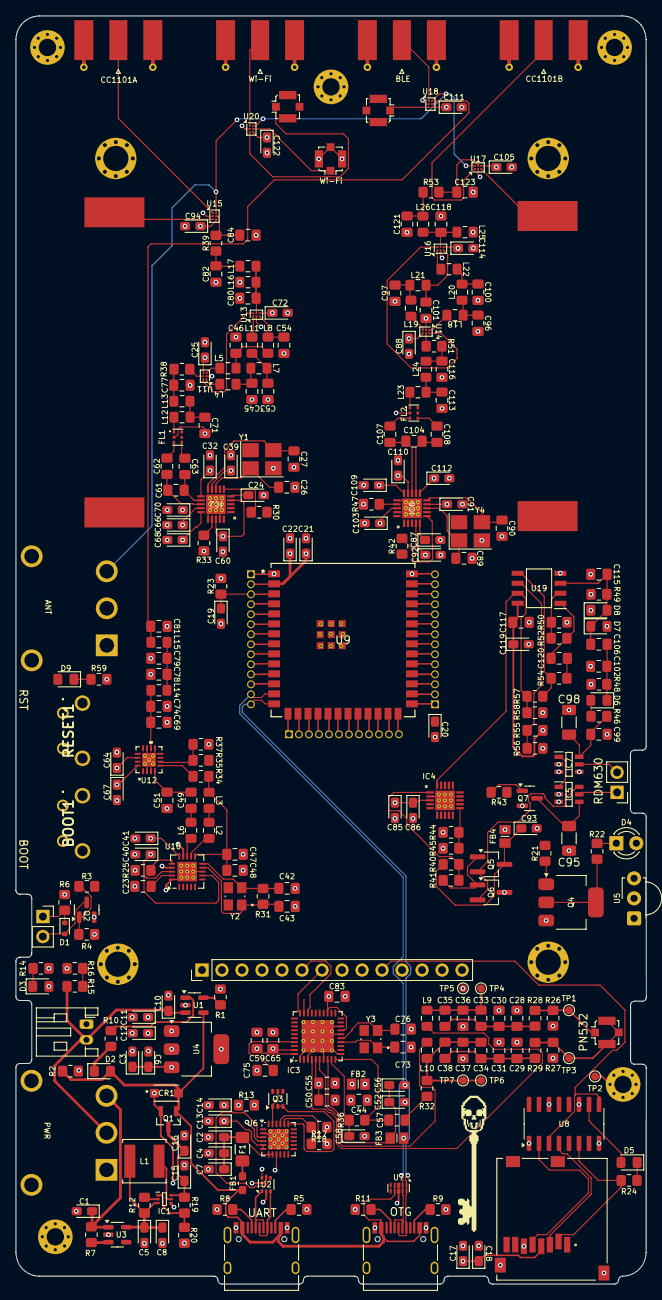
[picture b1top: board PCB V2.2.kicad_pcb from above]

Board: 4 copper layers, 80.0 x 161.0 mm, 298 parts (0 on the bottom side), 186 nets.
